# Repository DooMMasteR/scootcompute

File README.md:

scootcompute
============

A simple bord computer for scooters

It is arduino based and uses an LCD to display information

* air temperature: Dallas/Maxim DS18B20 1-wire themometer
* oil temperature: TI LM35 analog thermometer 
* battery current: Allegro AC709 current sensor
* voltage: on board ADC via voltage divider
* engine revs: via ICP interrupt of the ATmega

The display is ST7565 based but any display supported by U8Glib should more or less plug and play.

Pictures of the current state: http://goo.gl/qn9DZ

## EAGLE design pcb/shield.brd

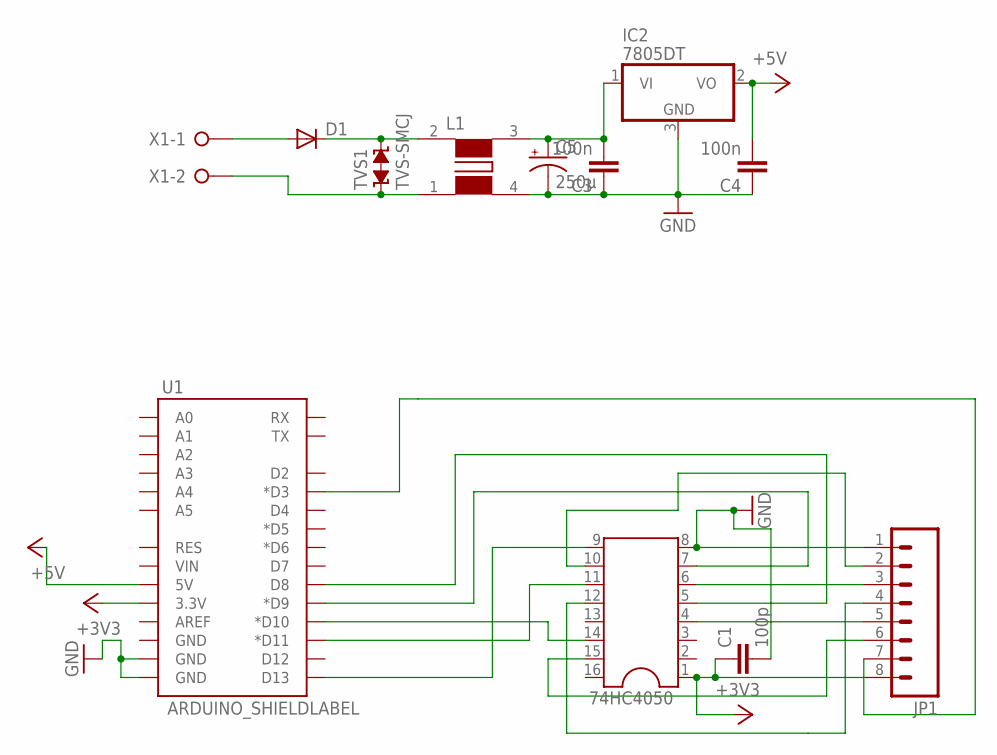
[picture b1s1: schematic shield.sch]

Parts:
74HC4050: DIL16
C1: 100p; C0603K
C3, C4: 100n; C1206K
C5: 250µ; PANASONIC_H13
D1: DIODE-DO-214AC; DO-214AC
IC2: 7805DT; TO252
JP1: M083.5MM-8; SCREWTERMINAL-3.5MM-8
L1: WE-SL2; WE-SL2_74422...
TVS1: TVS-SMCJ; SMCJ
U1: ARDUINO_SHIELDLABEL; DUEMILANOVE_SHIELD
X1: W237-02P; W237-132

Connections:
+3V3: 74HC4050.1, C1.1, JP1.8, U1.3.3V
+5V: C4.2, IC2.2 (VO), U1.5V
GND: 74HC4050.8, C1.2, C3.1, C4.1, C5.-, IC2.3 (GND), JP1.1, L1.4 (3), U1.GND@0 (GND), U1.GND@1 (GND)
unnamed: 74HC4050.9, U1.D13
unnamed: 74HC4050.11, U1.D11 (*D11)
unnamed: 74HC4050.14, U1.D10 (*D10)
unnamed: C3.2, C5.+, IC2.1 (VI), L1.3 (4)
unnamed: 74HC4050.7, U1.D9 (*D9)
unnamed: D1.C, L1.2 (1), TVS1.C (2)
unnamed: 74HC4050.5, U1.D8
unnamed: 74HC4050.10, JP1.2
unnamed: D1.A, X1.1
unnamed: L1.1 (2), TVS1.A (1), X1.2
unnamed: 74HC4050.6, JP1.3
unnamed: 74HC4050.12, JP1.4
unnamed: 74HC4050.4, JP1.5
unnamed: 74HC4050.15, JP1.6
unnamed: JP1.7, U1.D3 (*D3)

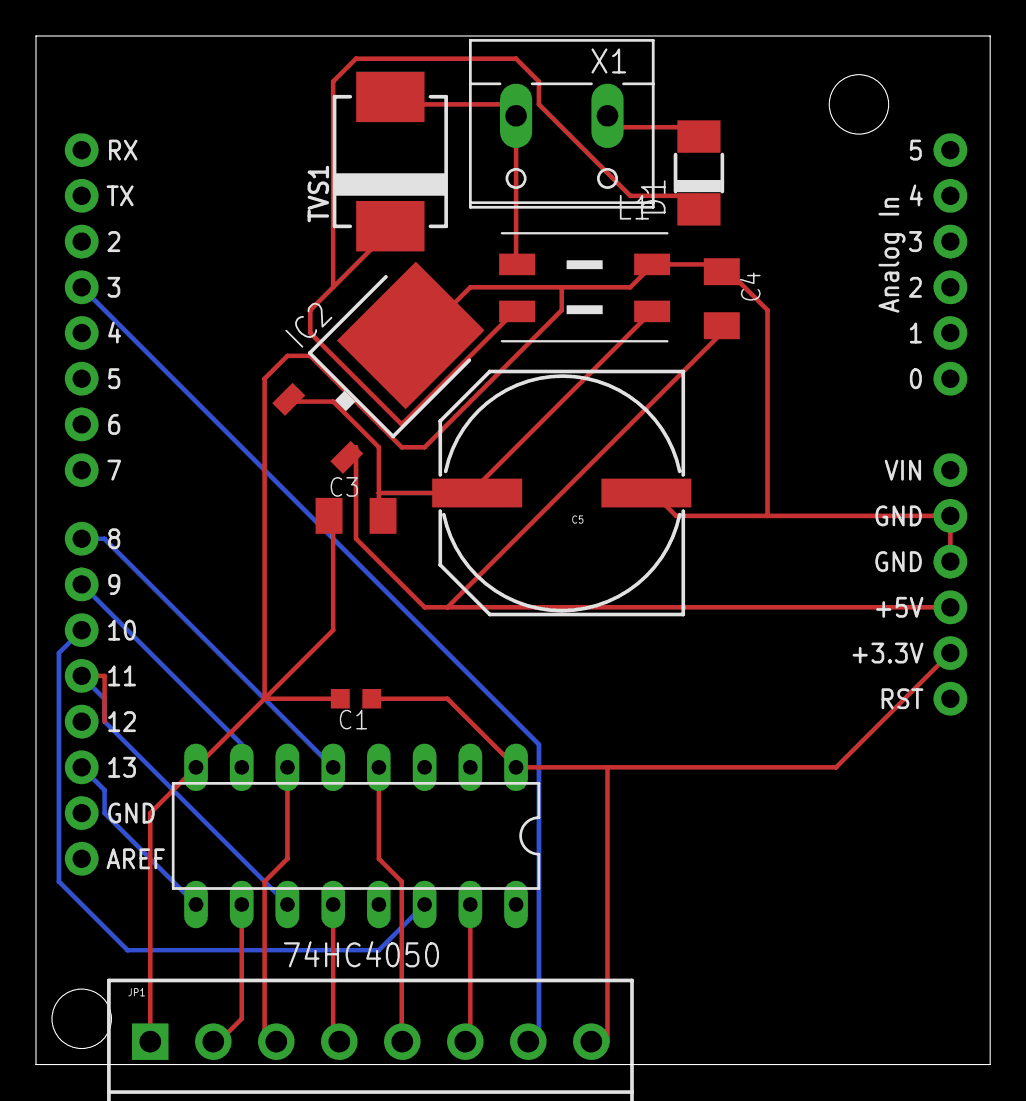
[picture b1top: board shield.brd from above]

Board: 2 copper layers, 53.0 x 57.1 mm, 12 parts (0 on the bottom side), 18 nets.

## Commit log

2012-12-19 intial commit in a working state
    but the rpm font is still broken and voltage is still unimplemented
2012-12-19 put res where they belong
2012-12-19 README readability
2012-12-19 add link to project gallery
2012-12-19 voltage reading implemented for 10:1 divider
2012-12-20 added basic pcb (only volt reg so far)
2012-12-22 moved the source and added pinheader for the display

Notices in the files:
parts and their libraries:
SparkFun: Licensing: CC v3.0 Share-Alike You are welcome to use this library for commercial purposes.
wuerth-elektronik: Copyright: Würth Elektronik eiSos
supressor: Copyright (C) 2009, Bob Starr
